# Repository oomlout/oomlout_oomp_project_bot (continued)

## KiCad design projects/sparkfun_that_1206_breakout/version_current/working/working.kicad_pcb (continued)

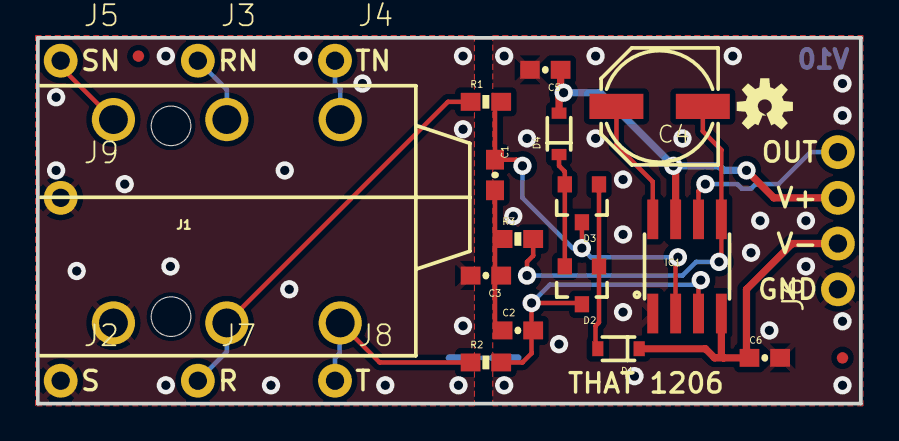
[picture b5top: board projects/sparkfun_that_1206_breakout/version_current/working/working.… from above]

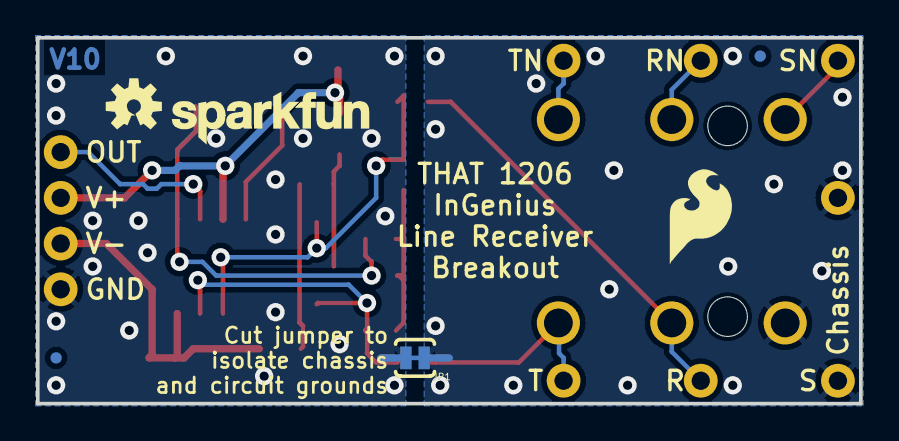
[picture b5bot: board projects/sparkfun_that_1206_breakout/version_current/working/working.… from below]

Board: 2 copper layers, 45.7 x 20.3 mm, 33 parts (6 on the bottom side), 17 nets.

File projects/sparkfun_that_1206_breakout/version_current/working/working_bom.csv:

"Id";"Designator";"Footprint";"Quantity";"Designation";"Supplier and ref";
1;"J6";"1X04_NO_SILK_ALL_ROUND";1;"1x4";;;
2;"C1,C2";"0603-CAP";2;"470pF";;;
3;"FD3,FD4,FD1,FD2";"MICRO-FIDUCIAL";4;"FIDUCIALUFIDUCIAL";;;
4;"D3,D2";"SOT23-3";2;"BAV99";;;
5;"J8";"1X01_NO_SILK";1;"T";;;
6;"R3";"0603-RES";1;"4.7K";;;
7;"C3";"0603-CAP";1;"100pF";;;
8;"J7";"1X01_NO_SILK";1;"R";;;
9;"D1,D4";"SOD-323";2;"12V";;;
10;"C5,C6";"0603-CAP";2;"0.1uF";;;
11;"FRAME1";"CREATIVE_COMMONS";1;"FRAME-LETTER";;;
12;"J3";"1X01_NO_SILK";1;"RN";;;
13;"LOGO4,LOGO3";"OSHW-LOGO-S";2;"OSHW-LOGOS";;;
14;"R2,R1";"0603-RES";2;"100";;;
15;"J5";"1X01_NO_SILK";1;"SN";;;
16;"J9";"1X01_NO_SILK";1;"Chassis";;;
17;"IC1";"SO08";1;"THAT1206";;;
18;"J2";"1X01_NO_SILK";1;"S";;;
19;"J4";"1X01_NO_SILK";1;"TN";;;
20;"J1";"AUDIO_JACK_0.25__TRS_PTH_RA";1;"INPUT";;;
21;"C4";"PANASONIC_D";1;"220uf";;;
22;"JP1";"PAD-JUMPER-2-NC_BY_TRACE_YES_SILK";1;"GND-JOIN";;;
23;"LOGO5";"SFE_LOGO_NAME_.1";1;"SFE_LOGO_NAME.1_INCH";;;
24;"LOGO2";"SFE_LOGO_FLAME_.2";1;"SFE_LOGO_FLAME.2_INCH";;;

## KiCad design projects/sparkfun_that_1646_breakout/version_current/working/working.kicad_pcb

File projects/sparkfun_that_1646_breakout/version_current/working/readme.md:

# THAT_1646_Breakout by sparkfun  
This is a harvested standardized copy of a project from github.  
The original project can be found at:  
https://github.com/sparkfun/THAT_1646_Breakout  
Please consult that link for additional, details, files, and license information.  
Note: It was auto harvested and if the original repo had more than one board file or anything out of the ordinary the files here are likely not representative.

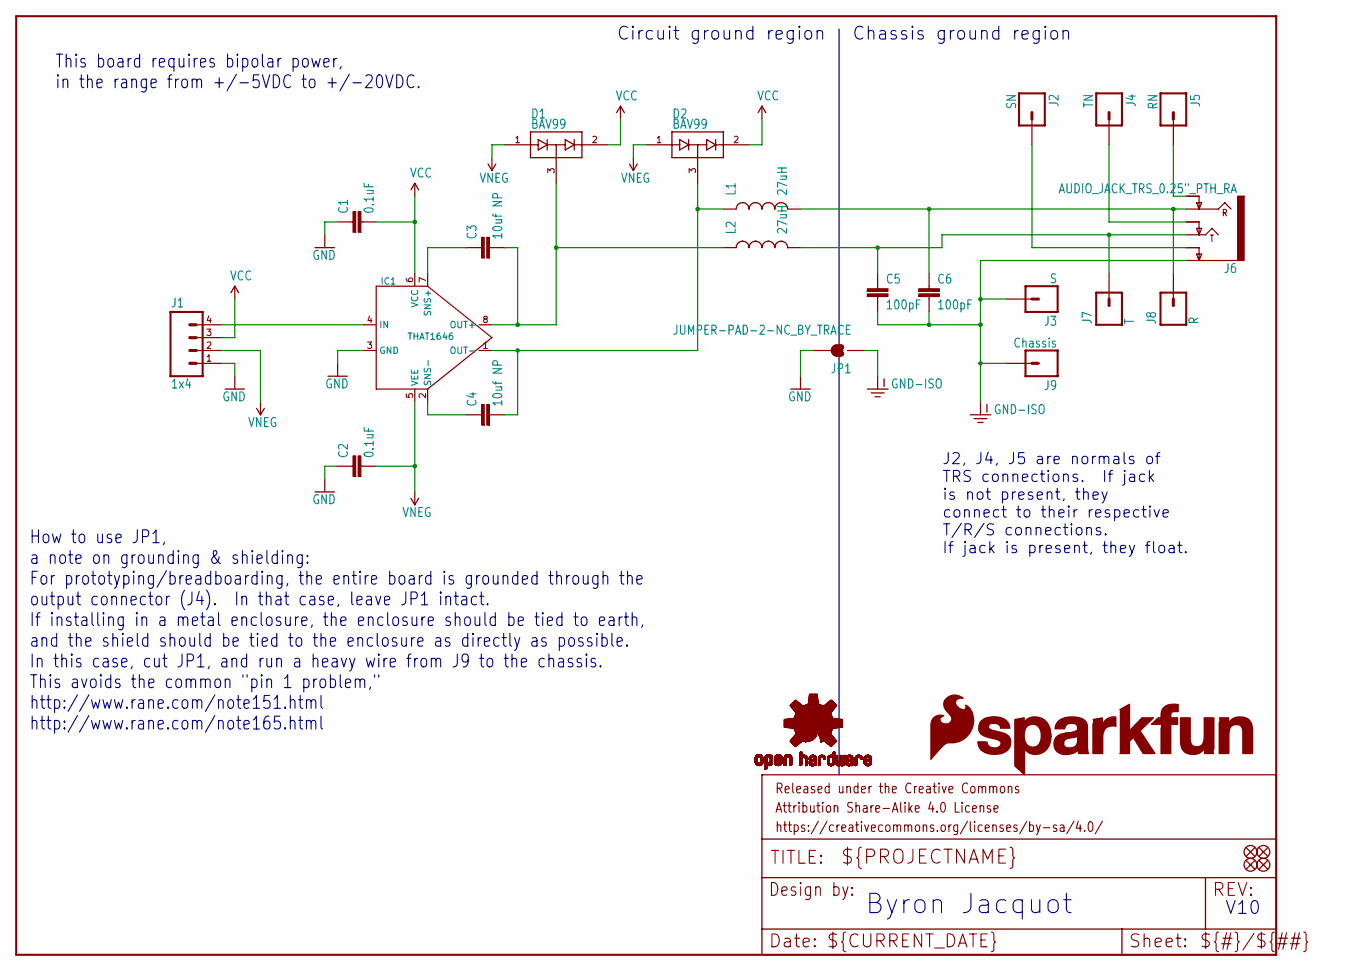
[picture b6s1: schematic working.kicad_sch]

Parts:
C1, C2: 0.1uF; 0603-CAP
C3, C4: 10uf NP; PANASONIC_D
C5, C6: 100pF; 0603-CAP
D1, D2: BAV99; SOT23-3
FD1, FD2, FD3, FD4: FIDUCIALUFIDUCIAL; MICRO-FIDUCIAL
FRAME1: FRAME-LETTER; CREATIVE_COMMONS
IC1: THAT1646; SO08
J1: 1x4; 1X04_NO_SILK_ALL_ROUND
J2: SN; 1X01_NO_SILK
J3: S; 1X01_NO_SILK
J4: TN; 1X01_NO_SILK
J5: RN; 1X01_NO_SILK
J6: AUDIO_JACK_TRS_0.25"_PTH_RA; AUDIO_JACK_0.25__TRS_PTH_RA
J7: T; 1X01_NO_SILK
J8: R; 1X01_NO_SILK
J9: Chassis; 1X01_NO_SILK
JP1: JUMPER-PAD-2-NC_BY_TRACE; PAD-JUMPER-2-NC_BY_TRACE_YES_SILK
L1, L2: 27uH; 0603
LOGO1, LOGO2: OSHW-LOGOS; OSHW-LOGO-S
LOGO4: SFE_LOGO_FLAME.2_INCH; SFE_LOGO_FLAME_.2
LOGO5: SFE_LOGO_NAME.1_INCH; SFE_LOGO_NAME_.1

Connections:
GND: C1.1, C2.1, IC1.3 (GND), J1.1, JP1.2
GND-ISO: C5.2, C6.2, J3.1, J6.SLEEVE (EARTH), J9.1, JP1.1
unnamed: J5.1, J6.RING-NORM
unnamed: J4.1, J6.TIP-NORM
unnamed: J2.1, J6.SLEEVE-NORM (EARTH-NORM)
unnamed: C5.1, J6.TIP, J7.1, L2.2
unnamed: C6.1, J6.RING, J8.1, L1.2
unnamed: C3.- (2), D1.3 (COM), IC1.8 (OUT+), L2.1
unnamed: C4.- (2), D2.3 (COM), IC1.1 (OUT-), L1.1
unnamed: C4.+ (1), IC1.2 (SNS-)
unnamed: C3.+ (1), IC1.7 (SNS+)
unnamed: IC1.4 (IN), J1.4
VCC: C1.2, D1.2 (C2), D2.2 (C2), IC1.6 (VCC), J1.3
VNEG: C2.2, D1.1 (A1), D2.1 (A1), IC1.5 (VEE), J1.2

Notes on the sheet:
How to use JP1, a note on grounding & shielding: For prototyping/breadboarding, the entire board is grounded through the output connector (J4). In that case, leave JP1 intact. If installing in a metal enclosure, the enclosure should be tied to earth, and the shield should be tied to the enclosure a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
Byron Jacquot
Circuit ground region
Chassis ground region
This board requires bipolar power, in the range from +/-5VDC to +/-20VDC.
V10
J2, J4, J5 are normals of TRS connections. If jack is not present, they connect to their respective T/R/S connections. If jack is present, they float.

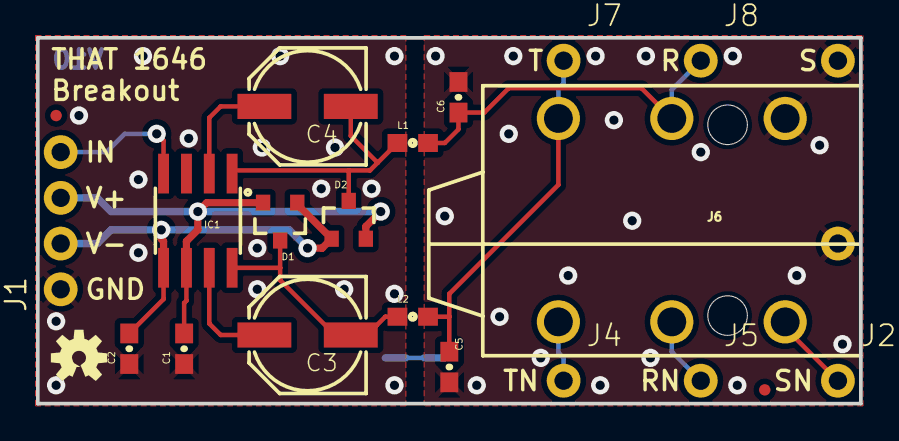
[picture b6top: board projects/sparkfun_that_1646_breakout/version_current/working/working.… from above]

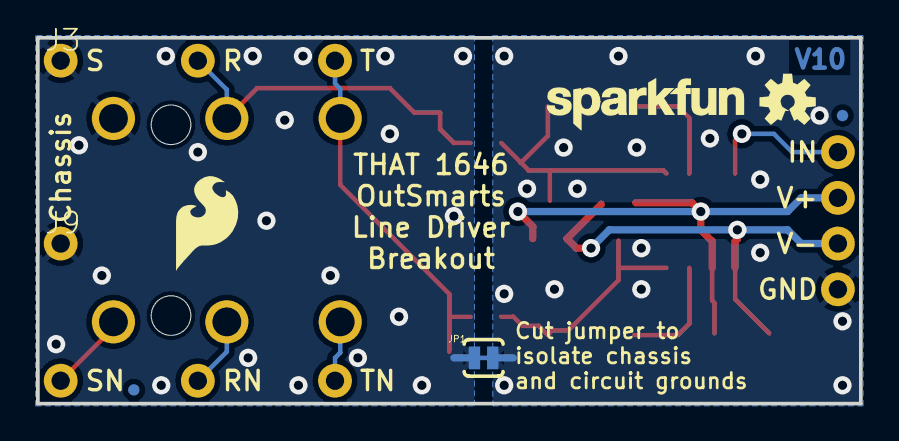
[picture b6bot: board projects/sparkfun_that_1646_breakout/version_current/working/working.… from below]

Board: 2 copper layers, 45.7 x 20.3 mm, 30 parts (8 on the bottom side), 14 nets.

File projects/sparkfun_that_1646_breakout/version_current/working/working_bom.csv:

"Id";"Designator";"Footprint";"Quantity";"Designation";"Supplier and ref";
1;"J6";"AUDIO_JACK_0.25__TRS_PTH_RA";1;"OUTPUT";;;
2;"L2,L1";"0603";2;"27uH";;;
3;"FRAME1";"CREATIVE_COMMONS";1;"FRAME-LETTER";;;
4;"C2,C1";"0603-CAP";2;"0.1uF";;;
5;"D2,D1";"SOT23-3";2;"BAV99";;;
6;"J2";"1X01_NO_SILK";1;"SN";;;
7;"FD3,FD4,FD2,FD1";"MICRO-FIDUCIAL";4;"FIDUCIALUFIDUCIAL";;;
8;"J4";"1X01_NO_SILK";1;"TN";;;
9;"IC1";"SO08";1;"THAT1646";;;
10;"J5";"1X01_NO_SILK";1;"RN";;;
11;"C5,C6";"0603-CAP";2;"100pF";;;
12;"J8";"1X01_NO_SILK";1;"R";;;
13;"J1";"1X04_NO_SILK_ALL_ROUND";1;"1x4";;;
14;"J7";"1X01_NO_SILK";1;"T";;;
15;"C3,C4";"PANASONIC_D";2;"10uf NP";;;
16;"LOGO1,LOGO2";"OSHW-LOGO-S";2;"OSHW-LOGOS";;;
17;"LOGO4";"SFE_LOGO_FLAME_.2";1;"SFE_LOGO_FLAME.2_INCH";;;
18;"LOGO5";"SFE_LOGO_NAME_.1";1;"SFE_LOGO_NAME.1_INCH";;;
19;"JP1";"PAD-JUMPER-2-NC_BY_TRACE_YES_SILK";1;"GND-JOIN";;;
20;"J9";"1X01_NO_SILK";1;"Chassis";;;
21;"J3";"1X01_NO_SILK";1;"S";;;

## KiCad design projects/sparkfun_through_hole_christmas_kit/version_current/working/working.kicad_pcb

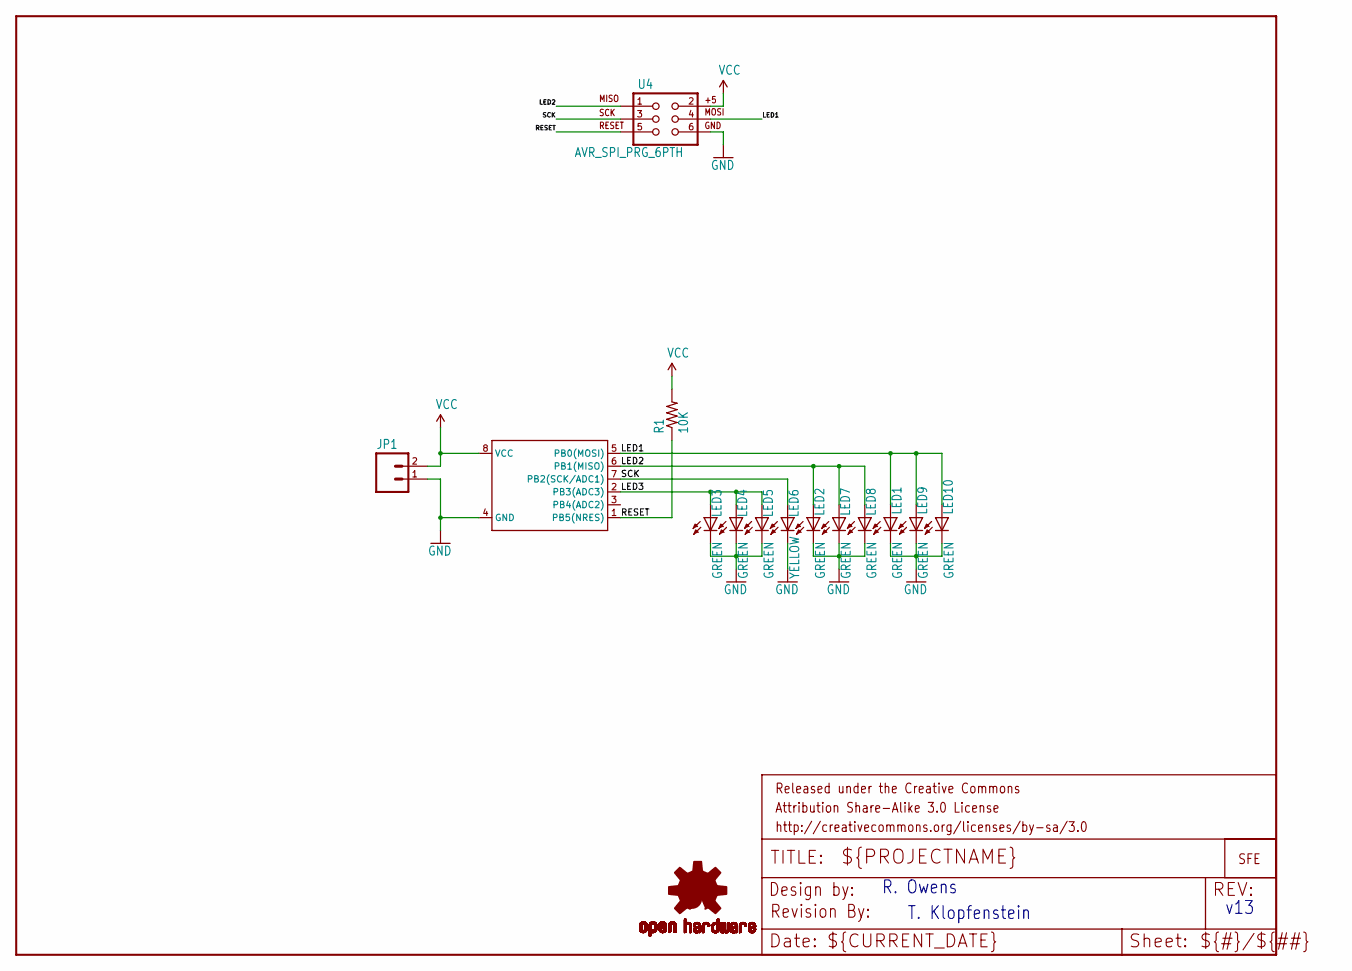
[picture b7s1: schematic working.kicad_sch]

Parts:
FRAME1: FRAME-LETTER; CREATIVE_COMMONS
JP1: M02PTH; 1X02
JP2: LOGO-SFENEW; SFE-NEW-WEBLOGO
LED1, LED2, LED3, LED4, LED5, LED7, LED8, LED9, LED10: GREEN; LED5MM
LED6: YELLOW; LED3MM
LOGO1: OSHW-LOGOL; OSHW-LOGO-L
R1: 10K; AXIAL-0.3
U2: ATTINY13DIP; DIP08
U4: AVR_SPI_PRG_6PTH; 2X3
U$1: REVISION

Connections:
GND: JP1.1, LED1.K (C), LED2.K (C), LED3.K (C), LED4.K (C), LED5.K (C), LED6.K (C), LED7.K (C), LED8.K (C), LED9.K (C), LED10.K (C), U2.4 (GND), U4.6
LED1: LED1.A, LED9.A, LED10.A, U2.5 (PB0(MOSI)), U4.4
LED2: LED2.A, LED7.A, LED8.A, U2.6 (PB1(MISO)), U4.1
LED3: LED3.A, LED4.A, LED5.A, U2.2 (PB3(ADC3))
RESET: R1.P$1 (1), U2.1 (PB5(NRES)), U4.5
SCK: LED6.A, U2.7 (PB2(SCK/ADC1)), U4.3
VCC: JP1.2, R1.P$2 (2), U2.8 (VCC), U4.2

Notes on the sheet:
T. Klopfenstein
R. Owens
v13

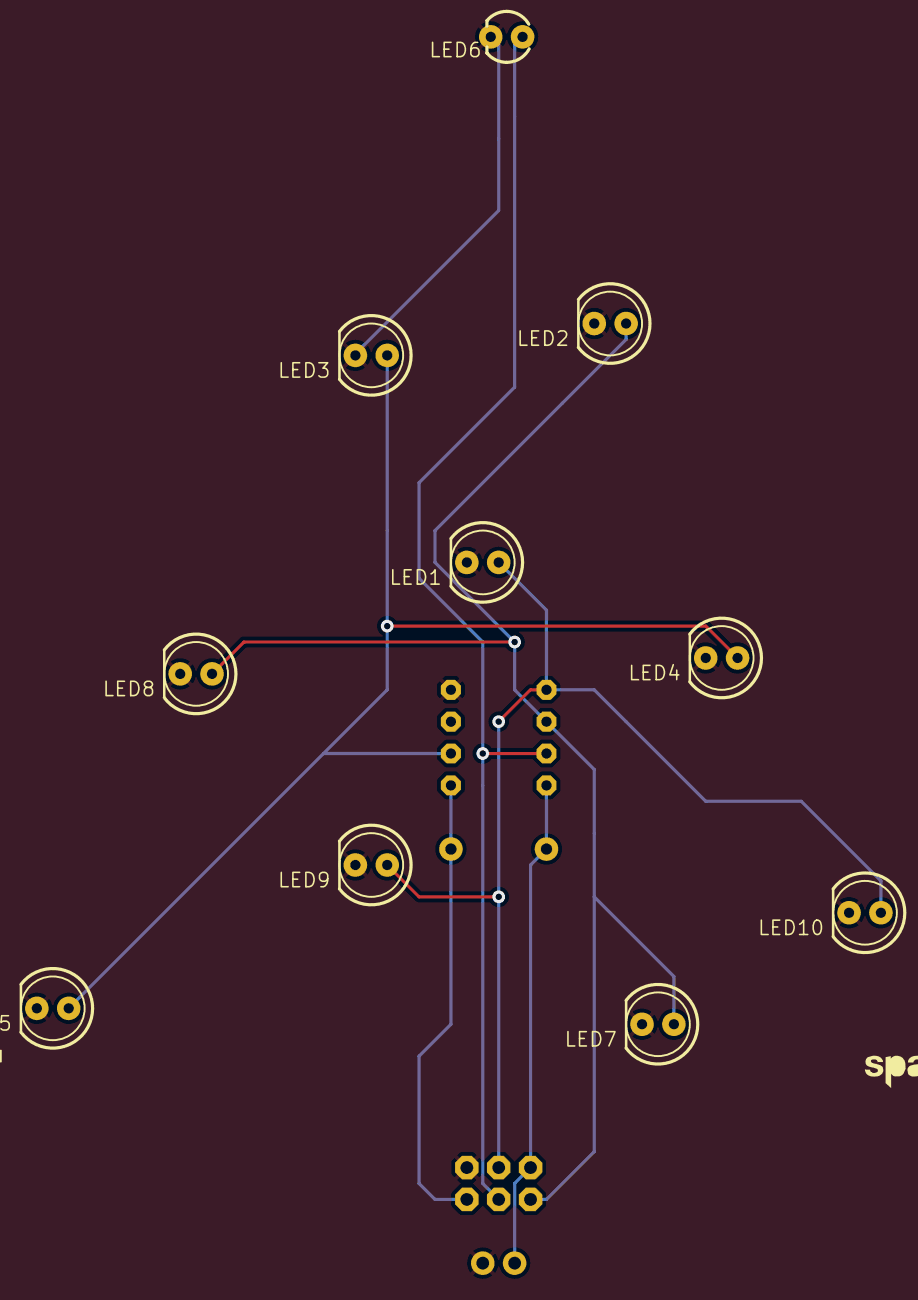
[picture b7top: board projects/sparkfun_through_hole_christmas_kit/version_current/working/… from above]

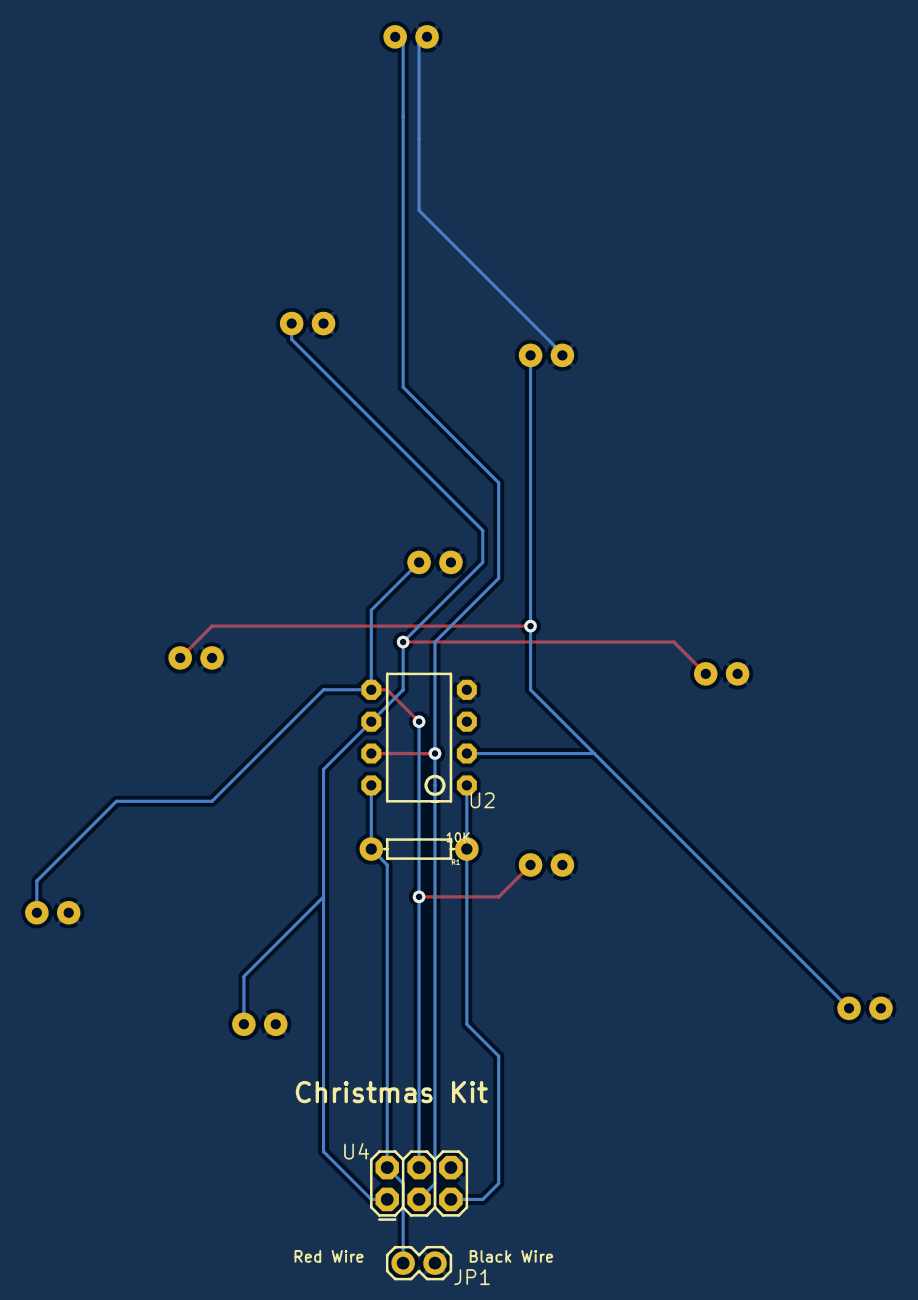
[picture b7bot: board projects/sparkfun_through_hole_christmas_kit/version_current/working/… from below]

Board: 2 copper layers, 19 parts (4 on the bottom side), 7 nets.

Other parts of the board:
@HOLE0: (no value)

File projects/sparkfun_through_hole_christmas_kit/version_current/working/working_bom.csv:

"Id";"Designator";"Footprint";"Quantity";"Designation";"Supplier and ref";
1;"LED3,LED5,LED10,LED9,LED8,LED1,LED2,LED4,LED7";"LED5MM";9;"GREEN";;;
2;"LED6";"LED3MM";1;"YELLOW";;;
3;"@HOLE0";"";1;"";;;
4;"LOGO1";"OSHW-LOGO-L";1;"OSHW-LOGOL";;;
5;"FRAME1";"CREATIVE_COMMONS";1;"FRAME-LETTER";;;
6;"U$1";"REVISION";1;"REVISION";;;
7;"JP2";"SFE-NEW-WEBLOGO";1;"LOGO-SFENEW";;;
8;"R1";"AXIAL-0.3";1;"10K";;;
9;"U4";"2X3";1;"AVR_SPI_PRG_6PTH";;;
10;"JP1";"1X02";1;"";;;
11;"U2";"DIP08";1;"ATTINY13DIP";;;
